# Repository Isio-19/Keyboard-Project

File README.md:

Install [ebastler's marbastlib](https://github.com/ebastler/marbastlib) library for the symbols and the footprints used in the schematics and PCB design respectively.

Kicad file for a keyboard with these features:
- Hotswapable
- Per-key RGB lighting
- Underglow lighting
- Split left shift
- ANSI enter
- Option between stepped and regular caps lock
- Option between a knob (Skyloong) or a switch
- Option between a full size space bar (6.25u) or split spacebars (2u + 2.25u + 2u)

To-do:
- [] Check if the capacitors, resistors and diodes have the right footprints
- [] Make a wireless version
- [] Make an Alice version

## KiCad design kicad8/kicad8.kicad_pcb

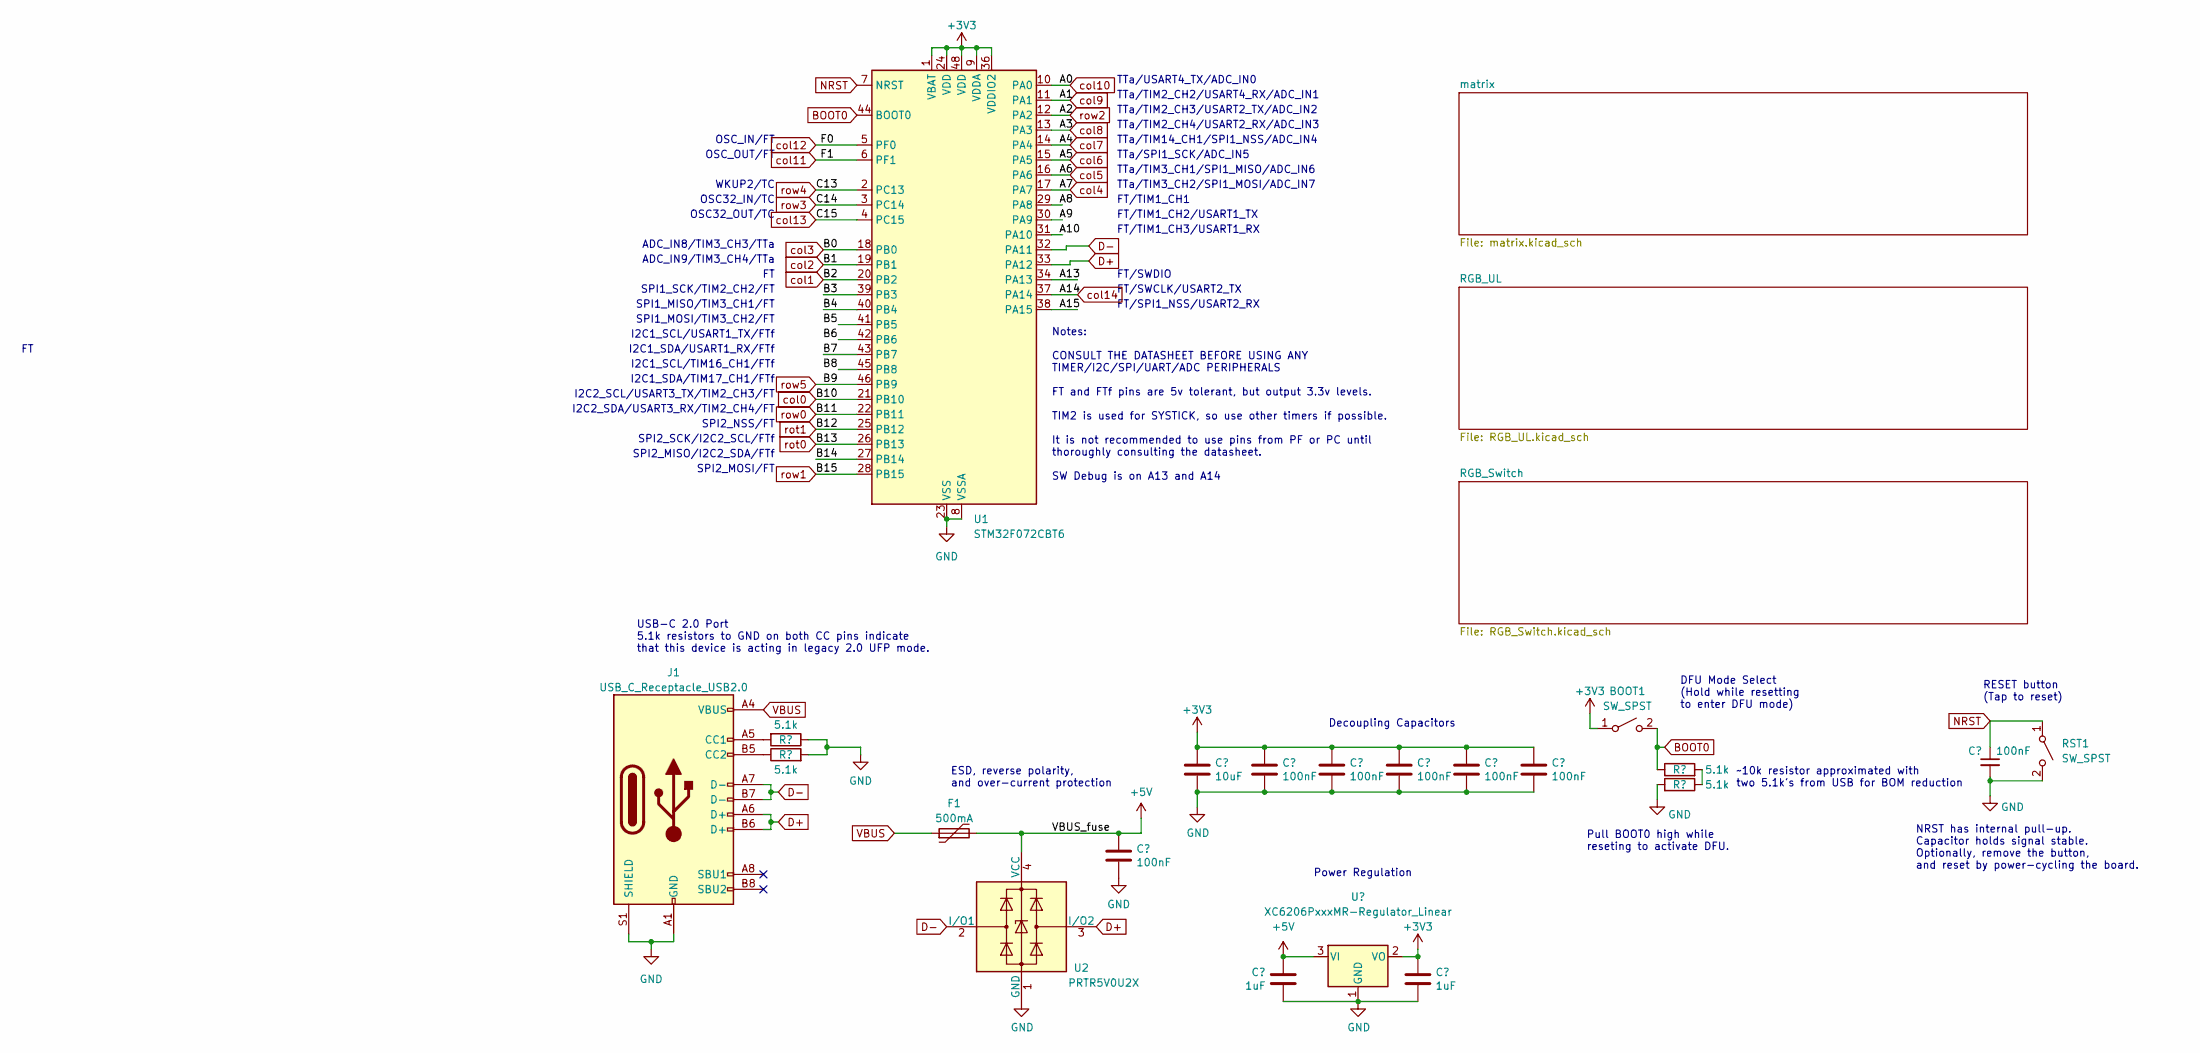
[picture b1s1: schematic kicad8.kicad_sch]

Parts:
BOOT1: SW_SPST; SW_SPST_TL3342
C1, C3, C4, C5, C6, C7, C8: 100nF; C_0402_1005Metric; LCSC C307331
C2: 10uF; C_0603_1608Metric; LCSC C307331
C9, C10: 1uF; C_0402_1005Metric; LCSC C307331
F1: 500mA; Fuse_1206_3216Metric; LCSC C135341
J1: USB_C_Receptacle_USB2.0; USB_C_Receptacle_HRO_TYPE-C-31-M-12; JlcRotOffset 180
R1, R2, R3, R4: 5.1k; R_0402_1005Metric
RST1: SW_SPST; SW_SPST_TL3342
U1: STM32F072CBT6; LQFP-48_7x7mm_P0.5mm; JlcRotOffset 90
U2: PRTR5V0U2X; SOT-143; LCSC C2827688
U3: XC6206PxxxMR-Regulator_Linear; SOT-23; LCSC C5446

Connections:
+3V3: BOOT1.1 (A), C2.1, C3.1, C4.1, C5.1, C6.1, C7.1, C10.1, U1.1 (VBAT), U1.9 (VDDA), U1.24 (VDD), U1.36 (VDDIO2), U1.48 (VDD), U3.2 (VO)
+5V: C8.1, C9.1, F1.2, U2.4 (VCC), U3.3 (VI); also elsewhere on the board
/A8: U1.29 (PA8)
/A9: U1.30 (PA9)
/A10: U1.31 (PA10)
/A13: U1.34 (PA13)
/A15: U1.38 (PA15)
/B3: U1.39 (PB3)
/B4: U1.40 (PB4)
/B5: U1.41 (PB5)
/B6: U1.42 (PB6)
/B7: U1.43 (PB7)
/B8: U1.45 (PB8)
/B14: U1.27 (PB14)
BOOT0: BOOT1.2 (B), R3.1, U1.44 (BOOT0)
D+: J1.A6 (D+), J1.B6 (D+), U1.33 (PA12), U2.3 (I/O2)
D-: J1.A7 (D-), J1.B7 (D-), U1.32 (PA11), U2.2 (I/O1)
GND: C1.2, C2.2, C3.2, C4.2, C5.2, C6.2, C7.2, C8.2, C9.2, C10.2, J1.A1 (GND), J1.A12 (GND), J1.B1 (GND), J1.B12 (GND), J1.S1 (SHIELD), R1.1, R2.2, R4.2, RST1.2 (B), U1.8 (VSSA), U1.23 (VSS), U1.35 (VSS), U1.47 (VSS), U2.1 (GND), U3.1 (GND); also elsewhere on the board
NRST: C1.1, RST1.1 (A), U1.7 (NRST)
unnamed: J1.A5 (CC1), R1.2
unnamed: J1.B5 (CC2), R2.1
unnamed: R3.2, R4.1
VBUS: F1.1, J1.A4 (VBUS), J1.A9 (VBUS), J1.B4 (VBUS), J1.B9 (VBUS)
col0: U1.21 (PB10); also elsewhere on the board
col1: U1.20 (PB2); also elsewhere on the board
col2: U1.19 (PB1); also elsewhere on the board
col3: U1.18 (PB0); also elsewhere on the board
col4: U1.17 (PA7); also elsewhere on the board
col5: U1.16 (PA6); also elsewhere on the board
col6: U1.15 (PA5); also elsewhere on the board
col7: U1.14 (PA4); also elsewhere on the board
col8: U1.13 (PA3); also elsewhere on the board
col9: U1.11 (PA1); also elsewhere on the board
col10: U1.10 (PA0); also elsewhere on the board
col11: U1.6 (PF1); also elsewhere on the board
col12: U1.5 (PF0); also elsewhere on the board
col13: U1.4 (PC15); also elsewhere on the board
col14: U1.37 (PA14); also elsewhere on the board
rot0: U1.26 (PB13); also elsewhere on the board
rot1: U1.25 (PB12); also elsewhere on the board
row0: U1.22 (PB11); also elsewhere on the board
row1: U1.28 (PB15); also elsewhere on the board
row2: U1.12 (PA2); also elsewhere on the board
row3: U1.3 (PC14); also elsewhere on the board
row4: U1.2 (PC13); also elsewhere on the board
row5: U1.46 (PB9); also elsewhere on the board

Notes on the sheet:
SPI1_SCK/TIM2_CH2/FT
FT/TIM1_CH1
FT/TIM1_CH3/USART1_RX
SPI2_NSS/FT
Notes: CONSULT THE DATASHEET BEFORE USING ANY TIMER/I2C/SPI/UART/ADC PERIPHERALS FT and FTf pins are 5v tolerant, but output 3.3v levels. TIM2 is used for SYSTICK, so use other timers if possible. It is not recommended to use pins from PF or PC until thoroughly consulting the datasheet. SW Debug is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
TTa/TIM2_CH4/USART2_RX/ADC_IN3
NRST has internal pull-up. Capacitor holds signal stable. Optionally, remove the button, and reset by power-cycling the board.
FT/SWDIO
Decoupling Capacitors
SPI1_MOSI/TIM3_CH2/FT
ADC_IN9/TIM3_CH4/TTa
I2C2_SCL/USART3_TX/TIM2_CH3/FT
SPI2_MISO/I2C2_SDA/FTf
FT/SWCLK/USART2_TX
I2C1_SCL/TIM16_CH1/FTf
~10k resistor approximated with two 5.1k's from USB for BOM reduction
TTa/TIM2_CH2/USART4_RX/ADC_IN1
USB-C 2.0 Port 5.1k resistors to GND on both CC pins indicate that this device is acting in legacy 2.0 UFP mode.
TTa/TIM2_CH3/USART2_TX/ADC_IN2
OSC_IN/FT
DFU Mode Select (Hold while resetting to enter DFU mode)
WKUP2/TC
I2C2_SDA/USART3_RX/TIM2_CH4/FT
ADC_IN8/TIM3_CH3/TTa
RESET button (Tap to reset)
Pull BOOT0 high while reseting to activate DFU.
I2C1_SDA/TIM17_CH1/FTf
TTa/SPI1_SCK/ADC_IN5
TTa/TIM3_CH1/SPI1_MISO/ADC_IN6
TTa/TIM3_CH2/SPI1_MOSI/ADC_IN7
OSC32_OUT/TC
FT/SPI1_NSS/USART2_RX
SPI1_MISO/TIM3_CH1/FT
OSC32_IN/TC
TTa/TIM14_CH1/SPI1_NSS/ADC_IN4
I2C1_SDA/USART1_RX/FTf
SPI2_MOSI/FT
FT/TIM1_CH2/USART1_TX
Power Regulation
SPI2_SCK/I2C2_SCL/FTf

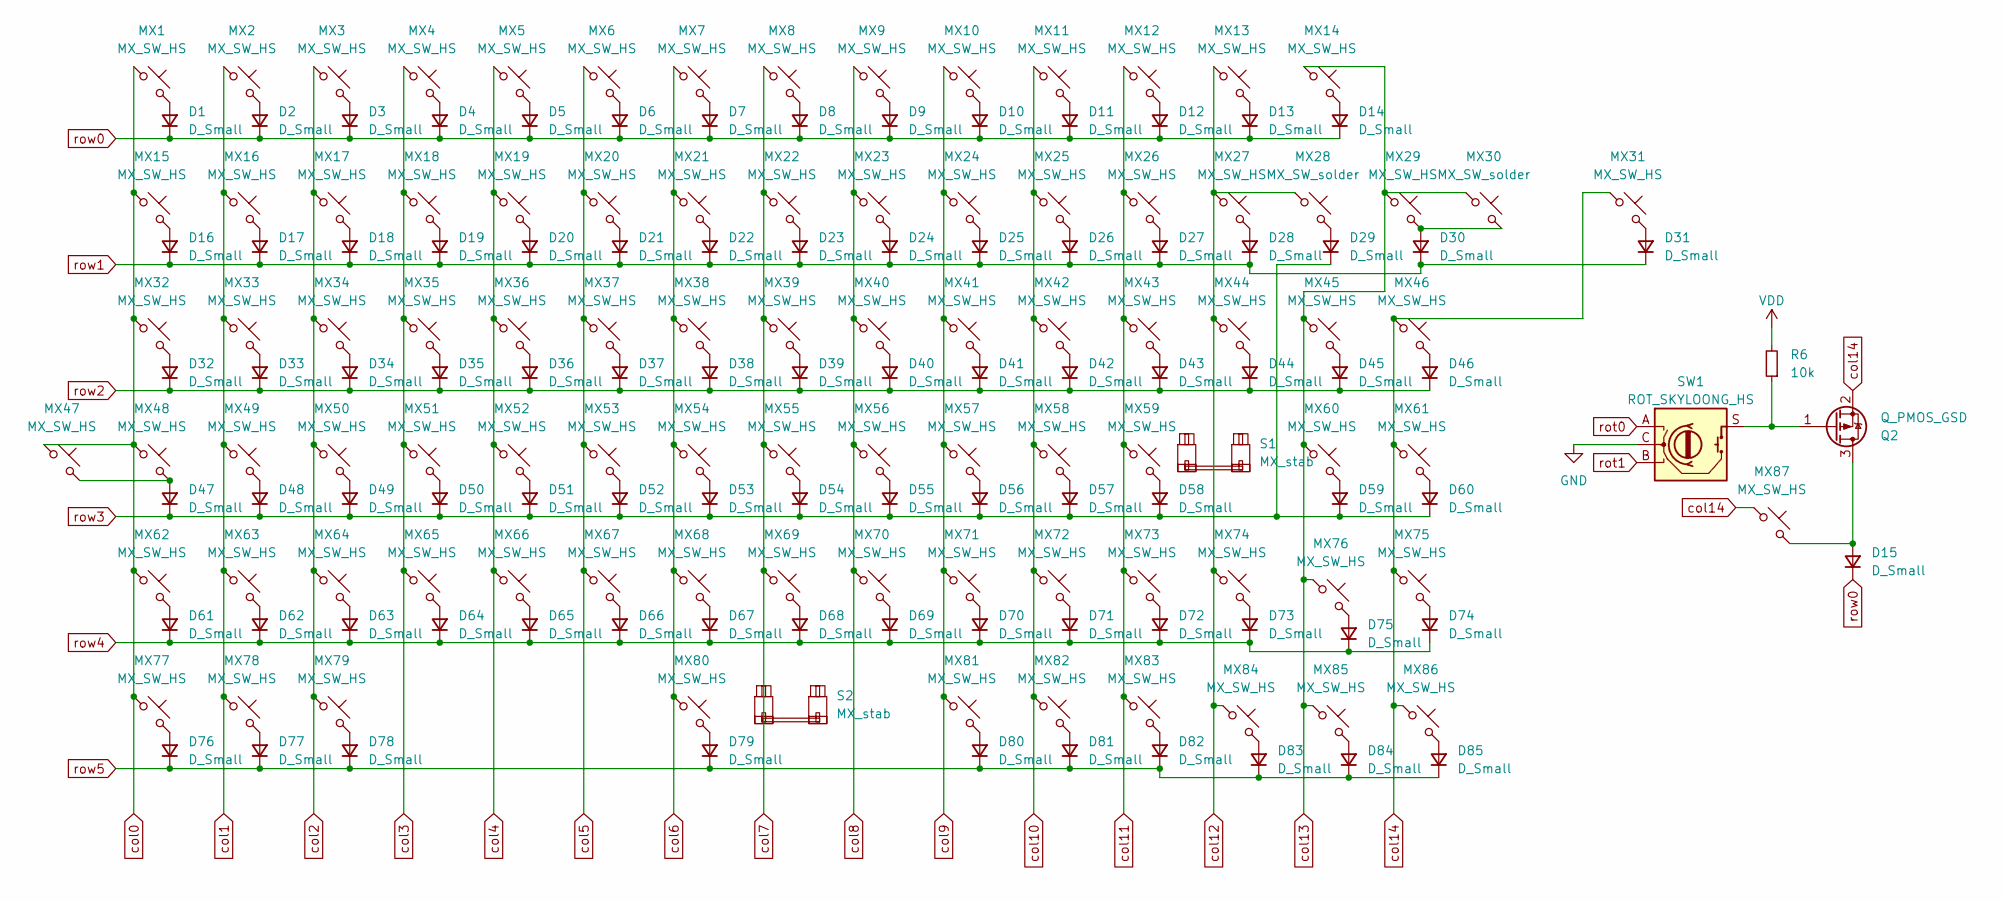
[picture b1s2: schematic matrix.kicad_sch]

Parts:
D1, D2, D3, D4, D5, D6, D7, D8, D9, D10, D11, D12, D13, D14, D15, D16, D17, D18, D19, D20, D21, D22, D23, D24, D25, D26, D27, D28, D29, D30, D31, D32, D33, D34, D35, D36, D37, D38, D39, D40, D41, D42, D43, D44, D45, D46, D47, D48, D49, D50, D51, D52, D53, D54, D55, D56, D57, D58, D59, D60, D61, D62, D63, D64, D65, D66, D67, D68, D69, D70, D71, D72, D73, D74, D75, D76, D77, D78, D79, D80, D81, D82, D83, D84, D85: D_Small; D_SOD-123
MX1, MX2, MX3, MX4, MX5, MX6, MX7, MX8, MX9, MX10, MX11, MX12, MX13, MX14, MX15, MX16, MX17, MX18, MX19, MX20, MX21, MX22, MX23, MX24, MX25, MX26, MX27, MX29, MX31, MX33, MX34, MX35, MX36, MX37, MX38, MX39, MX40, MX41, MX42, MX43, MX44, MX46, MX47, MX49, MX50, MX51, MX52, MX53, MX54, MX55, MX56, MX57, MX58, MX59, MX60, MX61, MX62, MX63, MX64, MX65, MX66, MX67, MX68, MX69, MX70, MX71, MX72, MX73, MX75, MX76, MX80, MX81, MX82, MX83, MX84, MX85, MX86, MX87: MX_SW_HS; SW_MX_HS_CPG151101S11_1u
MX28, MX30: MX_SW_solder; SW_MX_1u
MX32, MX45: MX_SW_HS; SW_MX_HS_CPG151101S11_1.5u
MX48: MX_SW_HS; SW_MX_HS_S_CPG151101S11_1u
MX74: MX_SW_HS; SW_MX_HS_CPG151101S11_1.75u
MX77, MX78, MX79: MX_SW_HS; SW_MX_HS_CPG151101S11_1.25u
Q2: Q_PMOS_GSD
R6: 10k; D_SOD-123
S1: MX_stab; STAB_MX_P_2.25u
S2: MX_stab; STAB_MX_P_6.25u
SW1: ROT_SKYLOONG_HS; ROT_SKYLOONG_HS-Switch

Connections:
GND: SW1.C; also elsewhere on the board
unnamed: D1.2 (A), MX1.2
unnamed: D2.2 (A), MX2.2
unnamed: D3.2 (A), MX3.2
unnamed: D4.2 (A), MX4.2
unnamed: D5.2 (A), MX5.2
unnamed: D6.2 (A), MX6.2
unnamed: D7.2 (A), MX7.2
unnamed: D8.2 (A), MX8.2
unnamed: D9.2 (A), MX9.2
unnamed: D10.2 (A), MX10.2
unnamed: D11.2 (A), MX11.2
unnamed: D12.2 (A), MX12.2
unnamed: D13.2 (A), MX13.2
unnamed: D14.2 (A), MX14.2
unnamed: D15.2 (A), MX87.2, Q2.3 (D)
unnamed: D16.2 (A), MX15.2
unnamed: D17.2 (A), MX16.2
unnamed: D18.2 (A), MX17.2
unnamed: D19.2 (A), MX18.2
unnamed: D20.2 (A), MX19.2
unnamed: D21.2 (A), MX20.2
unnamed: D22.2 (A), MX21.2
unnamed: D23.2 (A), MX22.2
unnamed: D24.2 (A), MX23.2
unnamed: D25.2 (A), MX24.2
unnamed: D26.2 (A), MX25.2
unnamed: D27.2 (A), MX26.2
unnamed: D28.2 (A), MX27.2
unnamed: D29.2 (A), MX28.2
unnamed: D30.2 (A), MX29.2, MX30.2
unnamed: D31.2 (A), MX31.2
unnamed: D32.2 (A), MX32.2
unnamed: D33.2 (A), MX33.2
unnamed: D34.2 (A), MX34.2
unnamed: D35.2 (A), MX35.2
unnamed: D36.2 (A), MX36.2
unnamed: D37.2 (A), MX37.2
unnamed: D38.2 (A), MX38.2
unnamed: D39.2 (A), MX39.2
unnamed: D40.2 (A), MX40.2
unnamed: D41.2 (A), MX41.2
unnamed: D42.2 (A), MX42.2
unnamed: D43.2 (A), MX43.2
unnamed: D44.2 (A), MX44.2
unnamed: D45.2 (A), MX45.2
unnamed: D46.2 (A), MX46.2
unnamed: D47.2 (A), MX47.2, MX48.2
unnamed: D48.2 (A), MX49.2
unnamed: D49.2 (A), MX50.2
unnamed: D50.2 (A), MX51.2
unnamed: D51.2 (A), MX52.2
unnamed: D52.2 (A), MX53.2
unnamed: D53.2 (A), MX54.2
unnamed: D54.2 (A), MX55.2
unnamed: D55.2 (A), MX56.2
unnamed: D56.2 (A), MX57.2
unnamed: D57.2 (A), MX58.2
unnamed: D58.2 (A), MX59.2
unnamed: D59.2 (A), MX60.2
unnamed: D60.2 (A), MX61.2
unnamed: D61.2 (A), MX62.2
unnamed: D62.2 (A), MX63.2
unnamed: D63.2 (A), MX64.2
unnamed: D64.2 (A), MX65.2
unnamed: D65.2 (A), MX66.2
unnamed: D66.2 (A), MX67.2
unnamed: D67.2 (A), MX68.2
unnamed: D68.2 (A), MX69.2
unnamed: D69.2 (A), MX70.2
unnamed: D70.2 (A), MX71.2
unnamed: D71.2 (A), MX72.2
unnamed: D72.2 (A), MX73.2
unnamed: D73.2 (A), MX74.2
unnamed: D74.2 (A), MX75.2
unnamed: D75.2 (A), MX76.2
unnamed: D76.2 (A), MX77.2
unnamed: D77.2 (A), MX78.2
unnamed: D78.2 (A), MX79.2
unnamed: D79.2 (A), MX80.2
unnamed: D80.2 (A), MX81.2
unnamed: D81.2 (A), MX82.2
unnamed: D82.2 (A), MX83.2
unnamed: D83.2 (A), MX84.2
unnamed: D84.2 (A), MX85.2
unnamed: D85.2 (A), MX86.2
unnamed: Q2.1 (G), R6.1, SW1.S
VDD: R6.2
col0: MX1.1, MX15.1, MX32.1, MX47.1, MX48.1, MX62.1, MX77.1; also elsewhere on the board
col1: MX2.1, MX16.1, MX33.1, MX49.1, MX63.1, MX78.1; also elsewhere on the board
col2: MX3.1, MX17.1, MX34.1, MX50.1, MX64.1, MX79.1; also elsewhere on the board
col3: MX4.1, MX18.1, MX35.1, MX51.1, MX65.1; also elsewhere on the board
col4: MX5.1, MX19.1, MX36.1, MX52.1, MX66.1; also elsewhere on the board
col5: MX6.1, MX20.1, MX37.1, MX53.1, MX67.1; also elsewhere on the board
col6: MX7.1, MX21.1, MX38.1, MX54.1, MX68.1, MX80.1; also elsewhere on the board
col7: MX8.1, MX22.1, MX39.1, MX55.1, MX69.1; also elsewhere on the board
col8: MX9.1, MX23.1, MX40.1, MX56.1, MX70.1; also elsewhere on the board
col9: MX10.1, MX24.1, MX41.1, MX57.1, MX71.1, MX81.1; also elsewhere on the board
col10: MX11.1, MX25.1, MX42.1, MX58.1, MX72.1, MX82.1; also elsewhere on the board
col11: MX12.1, MX26.1, MX43.1, MX59.1, MX73.1, MX83.1; also elsewhere on the board
col12: MX13.1, MX27.1, MX28.1, MX44.1, MX74.1, MX84.1; also elsewhere on the board
col13: MX14.1, MX29.1, MX30.1, MX45.1, MX60.1, MX76.1, MX85.1; also elsewhere on the board
col14: MX31.1, MX46.1, MX61.1, MX75.1, MX86.1, MX87.1, Q2.2 (S); also elsewhere on the board
rot0: SW1.A; also elsewhere on the board
rot1: SW1.B; also elsewhere on the board
row0: D1.1 (K), D2.1 (K), D3.1 (K), D4.1 (K), D5.1 (K), D6.1 (K), D7.1 (K), D8.1 (K), D9.1 (K), D10.1 (K), D11.1 (K), D12.1 (K), D13.1 (K), D14.1 (K), D15.1 (K); also elsewhere on the board
row1: D16.1 (K), D17.1 (K), D18.1 (K), D19.1 (K), D20.1 (K), D21.1 (K), D22.1 (K), D23.1 (K), D24.1 (K), D25.1 (K), D26.1 (K), D27.1 (K), D28.1 (K), D30.1 (K), D31.1 (K); also elsewhere on the board
row2: D32.1 (K), D33.1 (K), D34.1 (K), D35.1 (K), D36.1 (K), D37.1 (K), D38.1 (K), D39.1 (K), D40.1 (K), D41.1 (K), D42.1 (K), D43.1 (K), D44.1 (K), D45.1 (K), D46.1 (K); also elsewhere on the board
row3: D29.1 (K), D47.1 (K), D48.1 (K), D49.1 (K), D50.1 (K), D51.1 (K), D52.1 (K), D53.1 (K), D54.1 (K), D55.1 (K), D56.1 (K), D57.1 (K), D58.1 (K), D59.1 (K), D60.1 (K); also elsewhere on the board
row4: D61.1 (K), D62.1 (K), D63.1 (K), D64.1 (K), D65.1 (K), D66.1 (K), D67.1 (K), D68.1 (K), D69.1 (K), D70.1 (K), D71.1 (K), D72.1 (K), D73.1 (K), D74.1 (K), D75.1 (K); also elsewhere on the board
row5: D76.1 (K), D77.1 (K), D78.1 (K), D79.1 (K), D80.1 (K), D81.1 (K), D82.1 (K), D83.1 (K), D84.1 (K), D85.1 (K); also elsewhere on the board

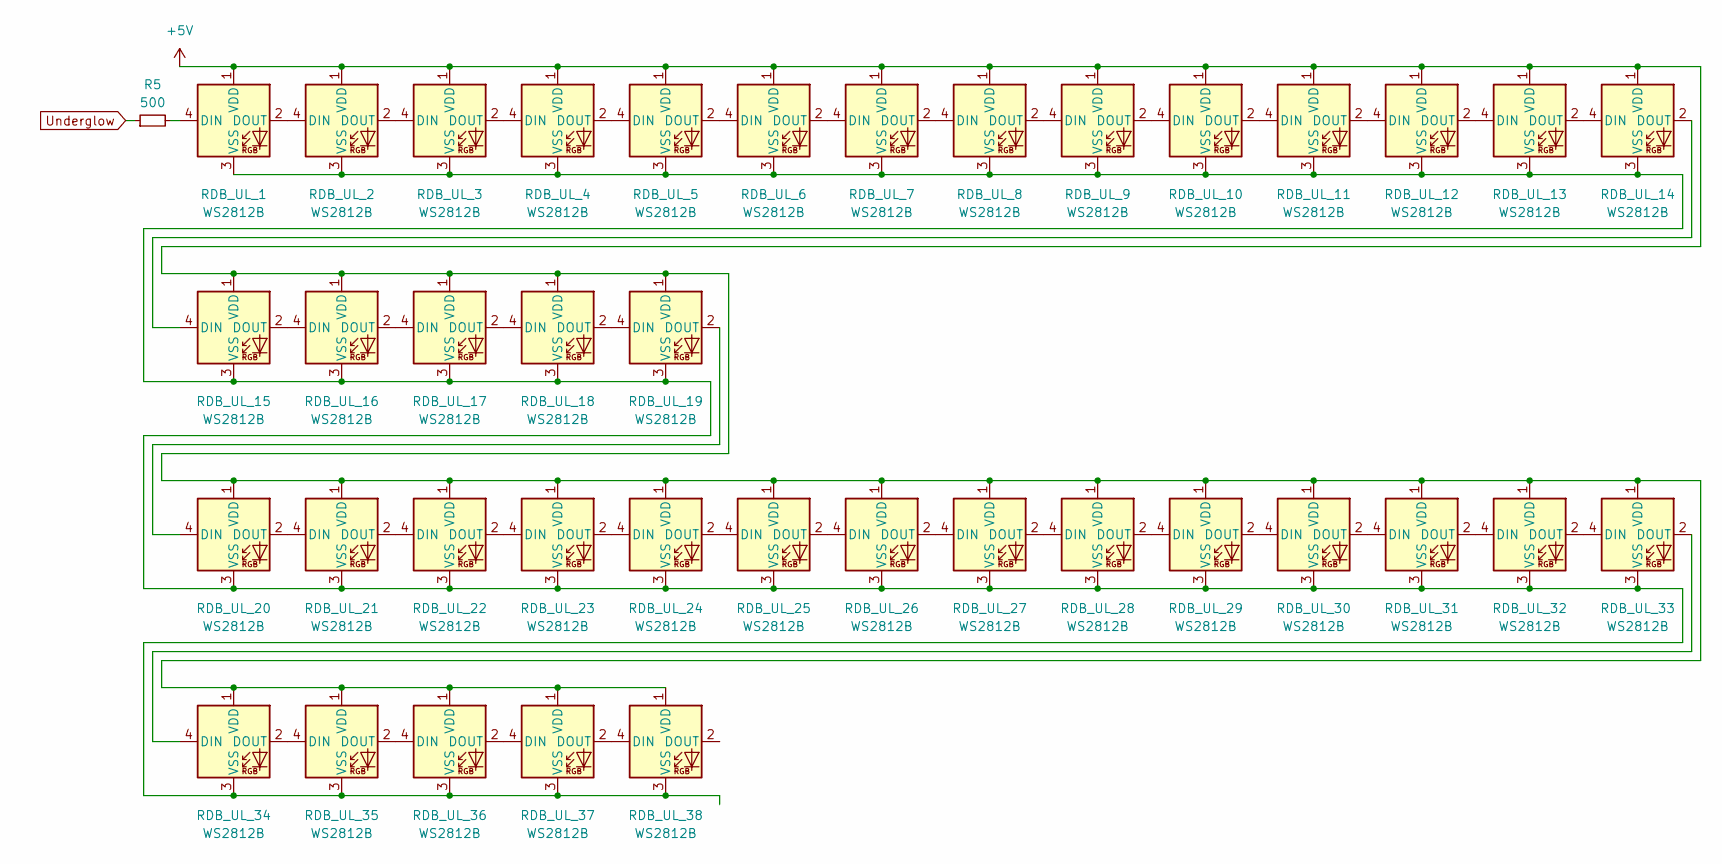
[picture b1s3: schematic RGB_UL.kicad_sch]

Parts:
R5: 500; D_SOD-123
RDB_UL_1, RDB_UL_2, RDB_UL_3, RDB_UL_4, RDB_UL_5, RDB_UL_6, RDB_UL_7, RDB_UL_8, RDB_UL_9, RDB_UL_10, RDB_UL_11, RDB_UL_12, RDB_UL_13, RDB_UL_14, RDB_UL_15, RDB_UL_16, RDB_UL_17, RDB_UL_18, RDB_UL_19, RDB_UL_20, RDB_UL_21, RDB_UL_22, RDB_UL_23, RDB_UL_24, RDB_UL_25, RDB_UL_26, RDB_UL_27, RDB_UL_28, RDB_UL_29, RDB_UL_30, RDB_UL_31, RDB_UL_32, RDB_UL_33, RDB_UL_34, RDB_UL_35, RDB_UL_36, RDB_UL_37, RDB_UL_38: WS2812B; LED_WS2812B_PLCC4_5.0x5.0mm_P3.2mm

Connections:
+5V: RDB_UL_1.1 (VDD), RDB_UL_2.1 (VDD), RDB_UL_3.1 (VDD), RDB_UL_4.1 (VDD), RDB_UL_5.1 (VDD), RDB_UL_6.1 (VDD), RDB_UL_7.1 (VDD), RDB_UL_8.1 (VDD), RDB_UL_9.1 (VDD), RDB_UL_10.1 (VDD), RDB_UL_11.1 (VDD), RDB_UL_12.1 (VDD), RDB_UL_13.1 (VDD), RDB_UL_14.1 (VDD), RDB_UL_15.1 (VDD), RDB_UL_16.1 (VDD), RDB_UL_17.1 (VDD), RDB_UL_18.1 (VDD), RDB_UL_19.1 (VDD), RDB_UL_20.1 (VDD), RDB_UL_21.1 (VDD), RDB_UL_22.1 (VDD), RDB_UL_23.1 (VDD), RDB_UL_24.1 (VDD), RDB_UL_25.1 (VDD), RDB_UL_26.1 (VDD), RDB_UL_27.1 (VDD), RDB_UL_28.1 (VDD), RDB_UL_29.1 (VDD), RDB_UL_30.1 (VDD), RDB_UL_31.1 (VDD), RDB_UL_32.1 (VDD), RDB_UL_33.1 (VDD), RDB_UL_34.1 (VDD), RDB_UL_35.1 (VDD), RDB_UL_36.1 (VDD), RDB_UL_37.1 (VDD), RDB_UL_38.1 (VDD); also elsewhere on the board
unnamed: R5.2, RDB_UL_1.4 (DIN)
unnamed: RDB_UL_1.2 (DOUT), RDB_UL_2.4 (DIN)
unnamed: RDB_UL_1.3 (VSS), RDB_UL_2.3 (VSS), RDB_UL_3.3 (VSS), RDB_UL_4.3 (VSS), RDB_UL_5.3 (VSS), RDB_UL_6.3 (VSS), RDB_UL_7.3 (VSS), RDB_UL_8.3 (VSS), RDB_UL_9.3 (VSS), RDB_UL_10.3 (VSS), RDB_UL_11.3 (VSS), RDB_UL_12.3 (VSS), RDB_UL_13.3 (VSS), RDB_UL_14.3 (VSS), RDB_UL_15.3 (VSS), RDB_UL_16.3 (VSS), RDB_UL_17.3 (VSS), RDB_UL_18.3 (VSS), RDB_UL_19.3 (VSS), RDB_UL_20.3 (VSS), RDB_UL_21.3 (VSS), RDB_UL_22.3 (VSS), RDB_UL_23.3 (VSS), RDB_UL_24.3 (VSS), RDB_UL_25.3 (VSS), RDB_UL_26.3 (VSS), RDB_UL_27.3 (VSS), RDB_UL_28.3 (VSS), RDB_UL_29.3 (VSS), RDB_UL_30.3 (VSS), RDB_UL_31.3 (VSS), RDB_UL_32.3 (VSS), RDB_UL_33.3 (VSS), RDB_UL_34.3 (VSS), RDB_UL_35.3 (VSS), RDB_UL_36.3 (VSS), RDB_UL_37.3 (VSS), RDB_UL_38.3 (VSS)
unnamed: RDB_UL_2.2 (DOUT), RDB_UL_3.4 (DIN)
unnamed: RDB_UL_3.2 (DOUT), RDB_UL_4.4 (DIN)
unnamed: RDB_UL_4.2 (DOUT), RDB_UL_5.4 (DIN)
unnamed: RDB_UL_5.2 (DOUT), RDB_UL_6.4 (DIN)
unnamed: RDB_UL_6.2 (DOUT), RDB_UL_7.4 (DIN)
unnamed: RDB_UL_7.2 (DOUT), RDB_UL_8.4 (DIN)
unnamed: RDB_UL_8.2 (DOUT), RDB_UL_9.4 (DIN)
unnamed: RDB_UL_9.2 (DOUT), RDB_UL_10.4 (DIN)
unnamed: RDB_UL_10.2 (DOUT), RDB_UL_11.4 (DIN)
unnamed: RDB_UL_11.2 (DOUT), RDB_UL_12.4 (DIN)
unnamed: RDB_UL_12.2 (DOUT), RDB_UL_13.4 (DIN)
unnamed: RDB_UL_13.2 (DOUT), RDB_UL_14.4 (DIN)
unnamed: RDB_UL_14.2 (DOUT), RDB_UL_15.4 (DIN)
unnamed: RDB_UL_15.2 (DOUT), RDB_UL_16.4 (DIN)
unnamed: RDB_UL_16.2 (DOUT), RDB_UL_17.4 (DIN)
unnamed: RDB_UL_17.2 (DOUT), RDB_UL_18.4 (DIN)
unnamed: RDB_UL_18.2 (DOUT), RDB_UL_19.4 (DIN)
unnamed: RDB_UL_19.2 (DOUT), RDB_UL_20.4 (DIN)
unnamed: RDB_UL_20.2 (DOUT), RDB_UL_21.4 (DIN)
unnamed: RDB_UL_21.2 (DOUT), RDB_UL_22.4 (DIN)
unnamed: RDB_UL_22.2 (DOUT), RDB_UL_23.4 (DIN)
unnamed: RDB_UL_23.2 (DOUT), RDB_UL_24.4 (DIN)
unnamed: RDB_UL_24.2 (DOUT), RDB_UL_25.4 (DIN)
unnamed: RDB_UL_25.2 (DOUT), RDB_UL_26.4 (DIN)
unnamed: RDB_UL_26.2 (DOUT), RDB_UL_27.4 (DIN)
unnamed: RDB_UL_27.2 (DOUT), RDB_UL_28.4 (DIN)
unnamed: RDB_UL_28.2 (DOUT), RDB_UL_29.4 (DIN)
unnamed: RDB_UL_29.2 (DOUT), RDB_UL_30.4 (DIN)
unnamed: RDB_UL_30.2 (DOUT), RDB_UL_31.4 (DIN)
unnamed: RDB_UL_31.2 (DOUT), RDB_UL_32.4 (DIN)
unnamed: RDB_UL_32.2 (DOUT), RDB_UL_33.4 (DIN)
unnamed: RDB_UL_33.2 (DOUT), RDB_UL_34.4 (DIN)
unnamed: RDB_UL_34.2 (DOUT), RDB_UL_35.4 (DIN)
unnamed: RDB_UL_35.2 (DOUT), RDB_UL_36.4 (DIN)
unnamed: RDB_UL_36.2 (DOUT), RDB_UL_37.4 (DIN)
unnamed: RDB_UL_37.2 (DOUT), RDB_UL_38.4 (DIN)
Underglow: R5.1

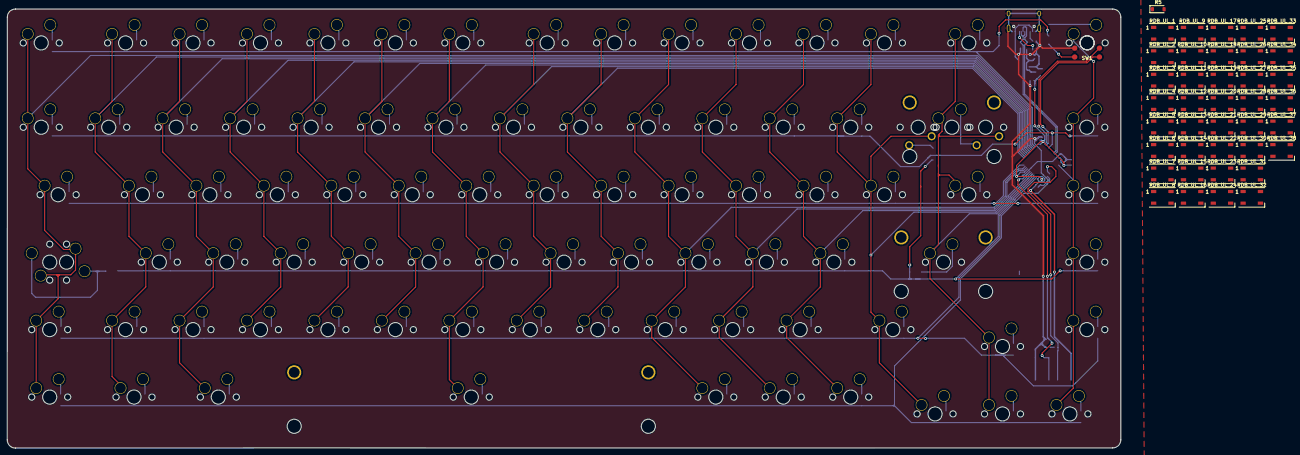
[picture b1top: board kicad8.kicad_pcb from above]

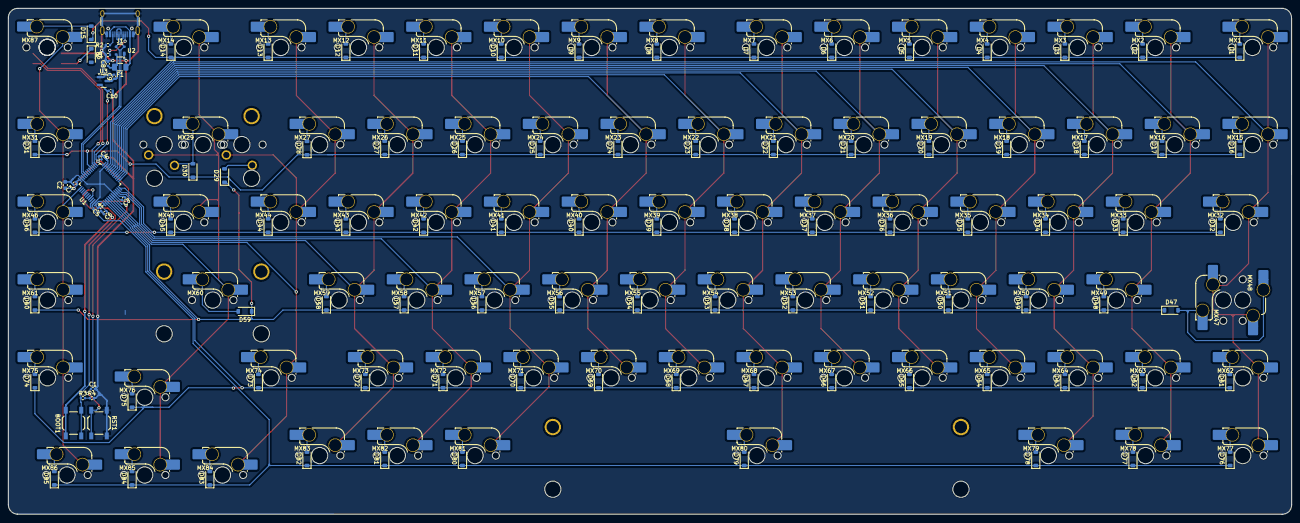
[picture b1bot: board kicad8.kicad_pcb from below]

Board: 2 copper layers, 314.5 x 124.0 mm, 237 parts (192 on the bottom side), 159 nets.

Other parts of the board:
S29: MX_stab; STAB_MX_P_2u

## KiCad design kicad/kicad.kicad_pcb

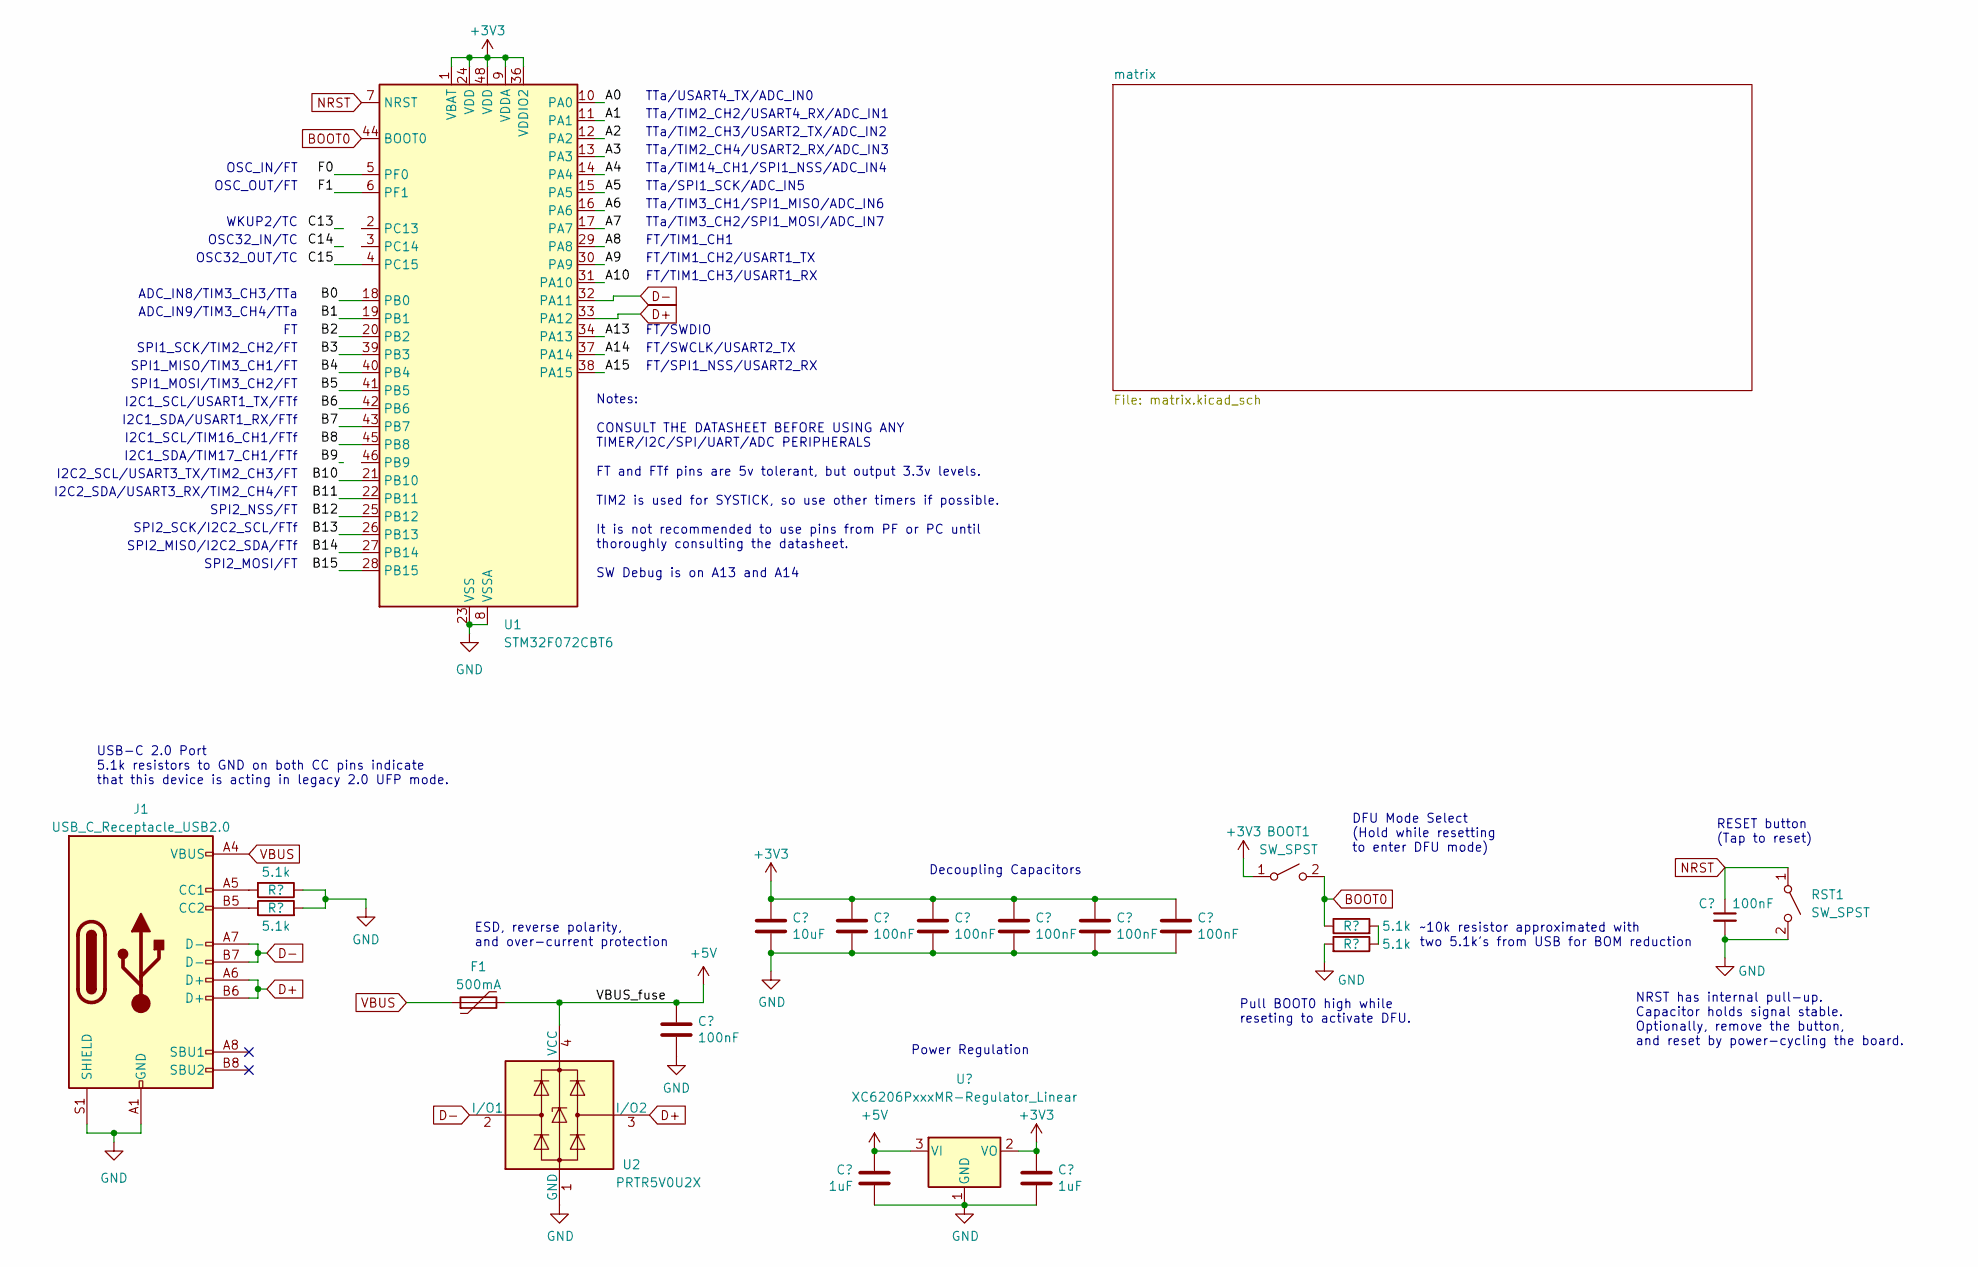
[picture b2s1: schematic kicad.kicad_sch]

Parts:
BOOT1: SW_SPST; SW_SPST_TL3342
C1, C3, C4, C5, C6, C7, C8: 100nF; C_0402_1005Metric; LCSC C307331
C2: 10uF; C_0603_1608Metric; LCSC C307331
C9, C10: 1uF; C_0402_1005Metric; LCSC C307331
F1: 500mA; Fuse_1206_3216Metric; LCSC C135341
J1: USB_C_Receptacle_USB2.0; USB_C_Receptacle_HRO_TYPE-C-31-M-12; JlcRotOffset 180
R1, R2, R3, R4: 5.1k; R_0402_1005Metric
RST1: SW_SPST; SW_SPST_TL3342
U1: STM32F072CBT6; LQFP-48_7x7mm_P0.5mm; JlcRotOffset 90
U2: PRTR5V0U2X; SOT-143; LCSC C2827688
U3: XC6206PxxxMR-Regulator_Linear; SOT-23; LCSC C5446

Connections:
+3V3: BOOT1.1 (A), C2.1, C3.1, C4.1, C5.1, C6.1, C7.1, C10.1, U1.1 (VBAT), U1.9 (VDDA), U1.24 (VDD), U1.36 (VDDIO2), U1.48 (VDD), U3.2 (VO)
+5V: C8.1, C9.1, F1.2, U2.4 (VCC), U3.3 (VI)
/A0: U1.10 (PA0)
/A1: U1.11 (PA1)
/A2: U1.12 (PA2)
/A3: U1.13 (PA3)
/A4: U1.14 (PA4)
/A5: U1.15 (PA5)
/A6: U1.16 (PA6)
/A7: U1.17 (PA7)
/A8: U1.29 (PA8)
/A9: U1.30 (PA9)
/A10: U1.31 (PA10)
/A13: U1.34 (PA13)
/A14: U1.37 (PA14)
/A15: U1.38 (PA15)
/B0: U1.18 (PB0)
/B1: U1.19 (PB1)
/B2: U1.20 (PB2)
/B3: U1.39 (PB3)
/B4: U1.40 (PB4)
/B5: U1.41 (PB5)
/B6: U1.42 (PB6)
/B7: U1.43 (PB7)
/B8: U1.45 (PB8)
/B10: U1.21 (PB10)
/B11: U1.22 (PB11)
/B12: U1.25 (PB12)
/B13: U1.26 (PB13)
/B14: U1.27 (PB14)
/B15: U1.28 (PB15)
/C15: U1.4 (PC15)
/F0: U1.5 (PF0)
/F1: U1.6 (PF1)
BOOT0: BOOT1.2 (B), R3.1, U1.44 (BOOT0)
D+: J1.A6 (D+), J1.B6 (D+), U1.33 (PA12), U2.3 (I/O2)
D-: J1.A7 (D-), J1.B7 (D-), U1.32 (PA11), U2.2 (I/O1)
GND: C1.2, C2.2, C3.2, C4.2, C5.2, C6.2, C7.2, C8.2, C9.2, C10.2, J1.A1 (GND), J1.A12 (GND), J1.B1 (GND), J1.B12 (GND), J1.S1 (SHIELD), R1.1, R2.2, R4.2, RST1.2 (B), U1.8 (VSSA), U1.23 (VSS), U1.35 (VSS), U1.47 (VSS), U2.1 (GND), U3.1 (GND)
NRST: C1.1, RST1.1 (A), U1.7 (NRST)
unnamed: J1.A5 (CC1), R1.2
unnamed: J1.B5 (CC2), R2.1
unnamed: R3.2, R4.1
VBUS: F1.1, J1.A4 (VBUS), J1.A9 (VBUS), J1.B4 (VBUS), J1.B9 (VBUS)

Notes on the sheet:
SPI1_SCK/TIM2_CH2/FT
FT/TIM1_CH1
FT/TIM1_CH3/USART1_RX
SPI2_NSS/FT
Notes: CONSULT THE DATASHEET BEFORE USING ANY TIMER/I2C/SPI/UART/ADC PERIPHERALS FT and FTf pins are 5v tolerant, but output 3.3v levels. TIM2 is used for SYSTICK, so use other timers if possible. It is not recommended to use pins from PF or PC until thoroughly consulting the datasheet. SW Debug is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
TTa/TIM2_CH4/USART2_RX/ADC_IN3
NRST has internal pull-up. Capacitor holds signal stable. Optionally, remove the button, and reset by power-cycling the board.
FT/SWDIO
Decoupling Capacitors
SPI1_MOSI/TIM3_CH2/FT
ADC_IN9/TIM3_CH4/TTa
I2C2_SCL/USART3_TX/TIM2_CH3/FT
SPI2_MISO/I2C2_SDA/FTf
FT/SWCLK/USART2_TX
I2C1_SCL/TIM16_CH1/FTf
~10k resistor approximated with two 5.1k's from USB for BOM reduction
TTa/TIM2_CH2/USART4_RX/ADC_IN1
USB-C 2.0 Port 5.1k resistors to GND on both CC pins indicate that this device is acting in legacy 2.0 UFP mode.
TTa/TIM2_CH3/USART2_TX/ADC_IN2
OSC_IN/FT
DFU Mode Select (Hold while resetting to enter DFU mode)
WKUP2/TC
I2C2_SDA/USART3_RX/TIM2_CH4/FT
ADC_IN8/TIM3_CH3/TTa
RESET button (Tap to reset)
Pull BOOT0 high while reseting to activate DFU.
I2C1_SDA/TIM17_CH1/FTf
TTa/SPI1_SCK/ADC_IN5
TTa/TIM3_CH1/SPI1_MISO/ADC_IN6
TTa/TIM3_CH2/SPI1_MOSI/ADC_IN7
OSC32_OUT/TC
FT/SPI1_NSS/USART2_RX
SPI1_MISO/TIM3_CH1/FT
OSC32_IN/TC
TTa/TIM14_CH1/SPI1_NSS/ADC_IN4
I2C1_SDA/USART1_RX/FTf
SPI2_MOSI/FT
FT/TIM1_CH2/USART1_TX
Power Regulation
SPI2_SCK/I2C2_SCL/FTf
